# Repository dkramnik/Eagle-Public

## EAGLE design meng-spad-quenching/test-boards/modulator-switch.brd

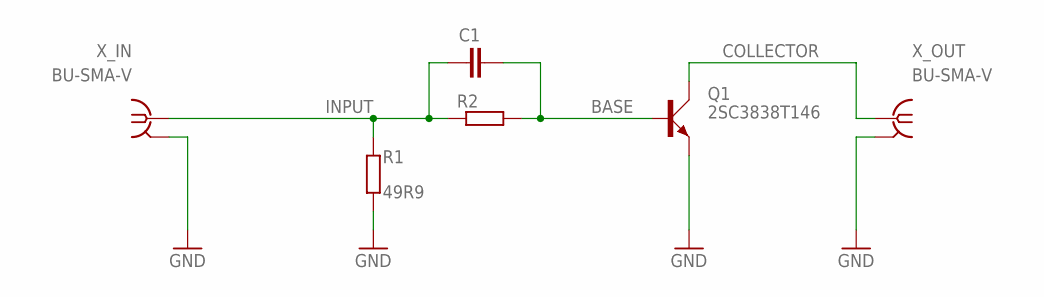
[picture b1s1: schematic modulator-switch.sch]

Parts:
C1: C-EUC0603; C0603
Q1: 2SC3838T146; SC59
R1: 49R9; R0805
R2: R-EU_R0603; R0603
X_IN: BU-SMA-V
X_OUT: BU-SMA-V

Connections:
BASE: C1.2, Q1.B, R2.2
COLLECTOR: Q1.C, X_OUT.1
GND: Q1.E, R1.2, X_IN.2 (GND), X_IN.3 (GND), X_IN.4 (GND), X_IN.5 (GND), X_OUT.2 (GND), X_OUT.3 (GND), X_OUT.4 (GND), X_OUT.5 (GND)
INPUT: C1.1, R1.1, R2.1, X_IN.1

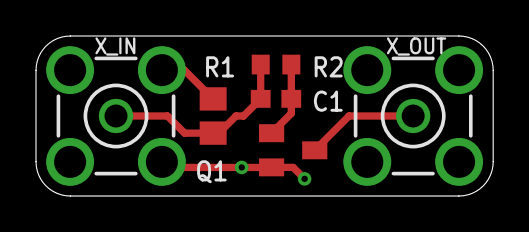
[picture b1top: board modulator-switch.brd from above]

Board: 2 copper layers, 25.4 x 8.9 mm, 6 parts (0 on the bottom side), 4 nets.

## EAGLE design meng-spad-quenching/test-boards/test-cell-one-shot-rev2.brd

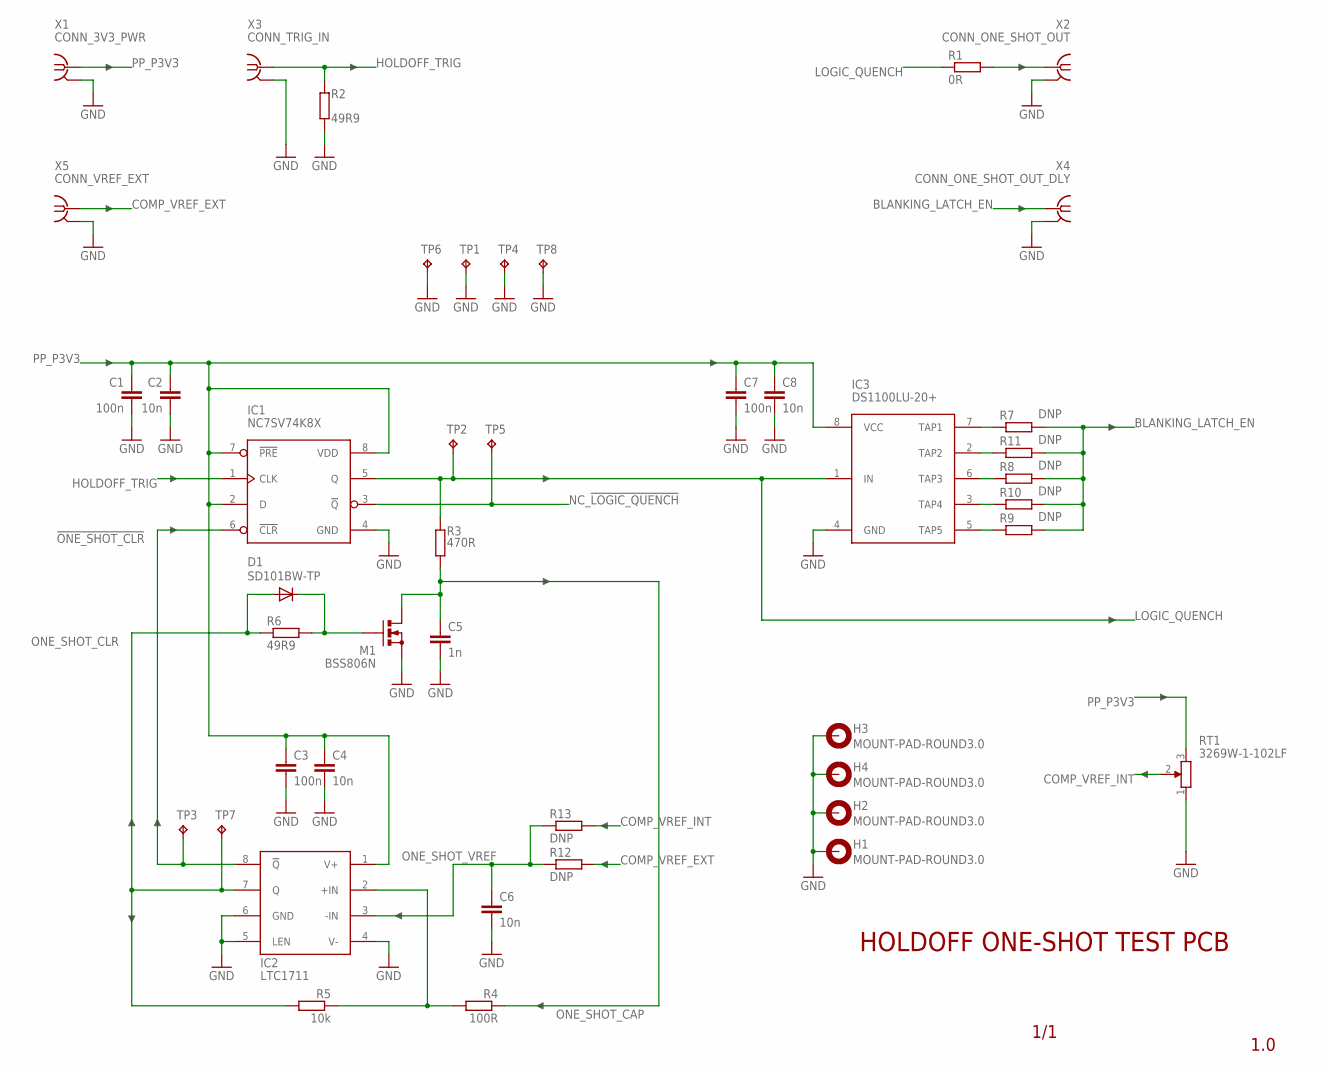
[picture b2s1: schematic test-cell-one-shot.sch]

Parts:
C1, C3, C7: 100n; C0402
C2, C4, C6, C8: 10n; C0402
C5: 1n; C0402
D1: SD101BW-TP; SOD123
H1, H2, H3, H4: MOUNT-PAD-ROUND3.0; 3,0-PAD
IC1: NC7SV74K8X; US8_3.1MM_JDEC_MO-187
IC2: LTC1711; US8_3.1MM_JDEC_MO-187
IC3: DS1100LU-20+; US8_3.1MM_JDEC_MO-187
M1: BSS806N; SOT23R_INFINEON
R1: 0R; R0402
R2: 49R9; R0603
R3: 470R; R0402
R4: 100R; R0402
R5: 10k; R0402
R6: 49R9; R0402
R7, R8, R9, R10, R11, R12, R13: DNP; R0402
RT1: 3269W-1-102LF; 3269W
TP1, TP2, TP3, TP4, TP5, TP6, TP7, TP8: TPTP10R; TP10R
X1: CONN_3V3_PWR; J502-ND-142-0711-871/876
X2: CONN_ONE_SHOT_OUT; J502-ND-142-0711-871/876
X3: CONN_TRIG_IN; J502-ND-142-0711-871/876
X4: CONN_ONE_SHOT_OUT_DLY; J502-ND-142-0711-871/876
X5: CONN_VREF_EXT; J502-ND-142-0711-871/876

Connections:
!ONE_SHOT_CLR: IC1.6 (!CLR), IC2.8 (!Q), TP3.TP
BLANKING_LATCH_EN: R7.1, R8.1, R9.1, R10.1, R11.1, X4.1
COMP_VREF_EXT: R12.1, X5.1
COMP_VREF_INT: R13.1, RT1.2
GND: C1.2, C2.2, C3.2, C4.2, C5.2, C6.2, C7.2, C8.2, H1.B3,0, H2.B3,0, H3.B3,0, H4.B3,0, IC1.4 (GND), IC2.4 (V-), IC2.5 (LEN), IC2.6 (GND), IC3.4 (GND), M1.2 (S), R2.2, RT1.1, TP1.TP, TP4.TP, TP6.TP, TP8.TP, X1.G@1 (GND), X1.G@2 (GND), X1.G@3 (GND), X1.G@4 (GND), X2.G@1 (GND), X2.G@2 (GND), X2.G@3 (GND), X2.G@4 (GND), X3.G@1 (GND), X3.G@2 (GND), X3.G@3 (GND), X3.G@4 (GND), X4.G@1 (GND), X4.G@2 (GND), X4.G@3 (GND), X4.G@4 (GND), X5.G@1 (GND), X5.G@2 (GND), X5.G@3 (GND), X5.G@4 (GND)
HOLDOFF_TRIG: IC1.1 (CLK), R2.1, X3.1
LOGIC_QUENCH: IC1.5 (Q), IC3.1 (IN), R1.2, R3.2, TP2.TP
unnamed: IC3.5 (TAP5), R9.2
unnamed: D1.C, M1.1 (G), R6.1
unnamed: R1.1, X2.1
unnamed: IC3.3 (TAP4), R10.2
unnamed: IC3.6 (TAP3), R8.2
unnamed: IC2.2 (+IN), R4.1, R5.2
unnamed: IC3.2 (TAP2), R11.2
unnamed: IC3.7 (TAP1), R7.2
NC_!LOGIC_QUENCH: IC1.3 (!Q), TP5.TP
ONE_SHOT_CAP: C5.1, M1.3 (D), R3.1, R4.2
ONE_SHOT_CLR: D1.A, IC2.7 (Q), R5.1, R6.2, TP7.TP
ONE_SHOT_VREF: C6.1, IC2.3 (-IN), R12.2, R13.2
PP_P3V3: C1.1, C2.1, C3.1, C4.1, C7.1, C8.1, IC1.2 (D), IC1.7 (!PRE), IC1.8 (VDD), IC2.1 (V+), IC3.8 (VCC), RT1.3, X1.1

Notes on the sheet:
HOLDOFF ONE-SHOT TEST PCB
1/1
1.0

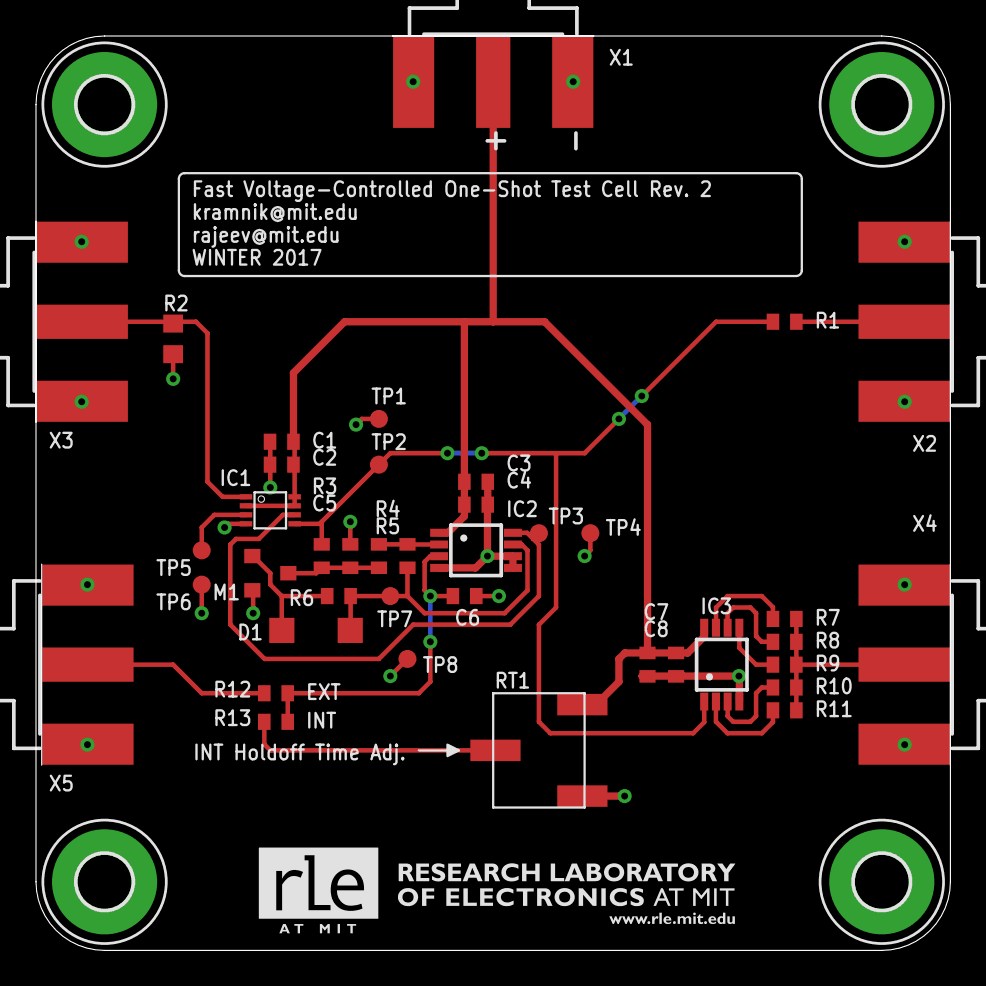
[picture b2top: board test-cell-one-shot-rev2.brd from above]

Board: 2 copper layers, 50.8 x 50.8 mm, 44 parts (0 on the bottom side), 20 nets.

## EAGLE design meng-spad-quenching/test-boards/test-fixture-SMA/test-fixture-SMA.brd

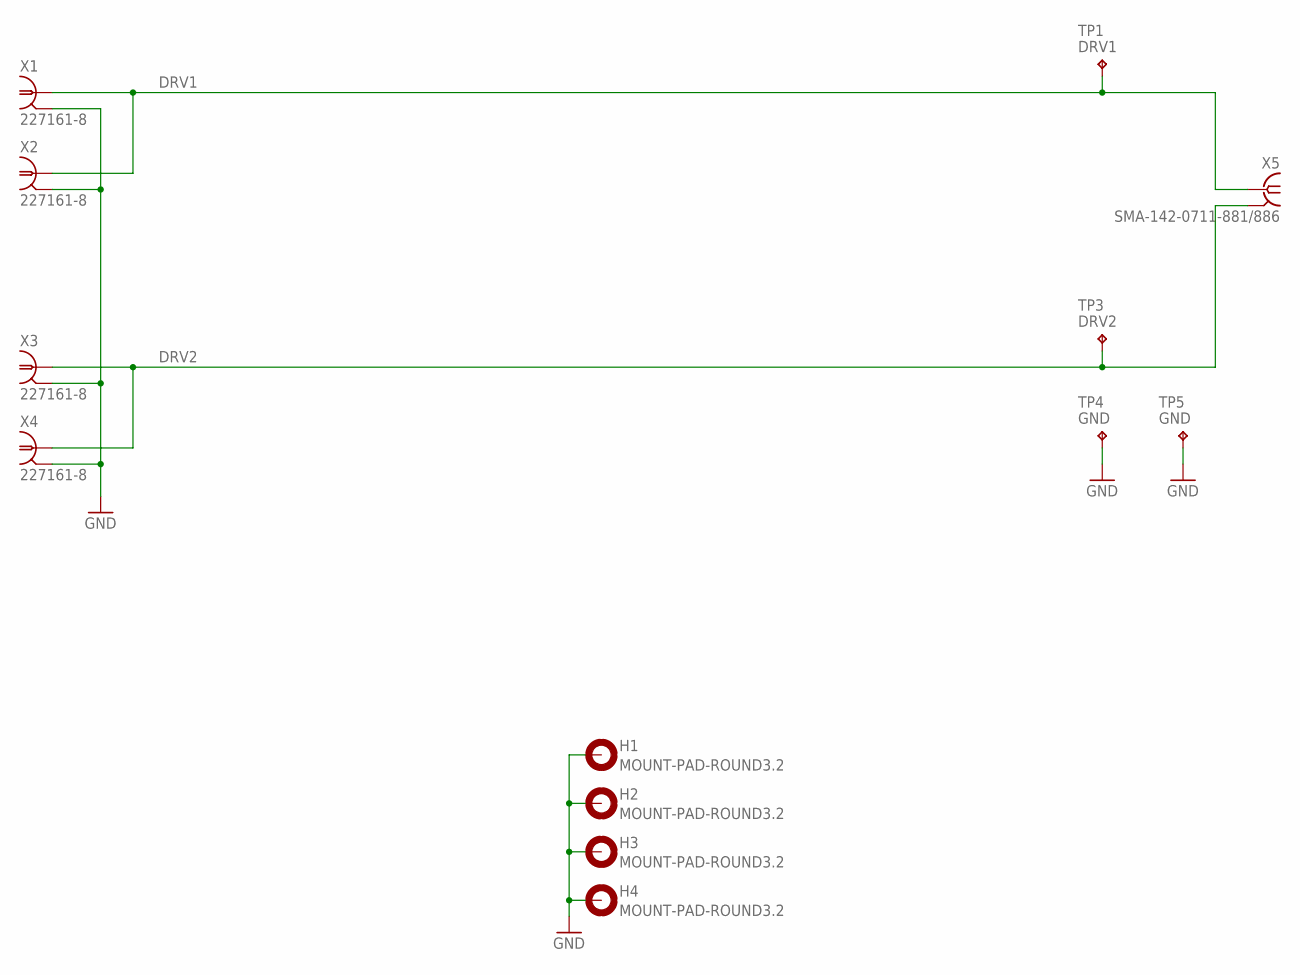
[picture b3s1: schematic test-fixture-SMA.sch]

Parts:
H1, H2, H3, H4: MOUNT-PAD-ROUND3.2; 3,2-PAD
TP1: DRV1; KEYSTONE_5000_MINIATURE
TP3: DRV2; KEYSTONE_5000_MINIATURE
TP4, TP5: GND; KEYSTONE_5000_MINIATURE
X1, X2, X3, X4: 227161-8; AMP_227161
X5: SMA-142-0711-881/886; J502-ND-142-0711-881/886

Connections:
DRV1: TP1.P$1, X1.1, X2.1, X5.1
DRV2: TP3.P$1, X3.1, X4.1, X5.G@1 (2), X5.G@2 (2), X5.G@3 (2), X5.G@4 (2)
GND: H1.B3,2, H2.B3,2, H3.B3,2, H4.B3,2, TP4.P$1, TP5.P$1, X1.2, X2.2, X3.2, X4.2

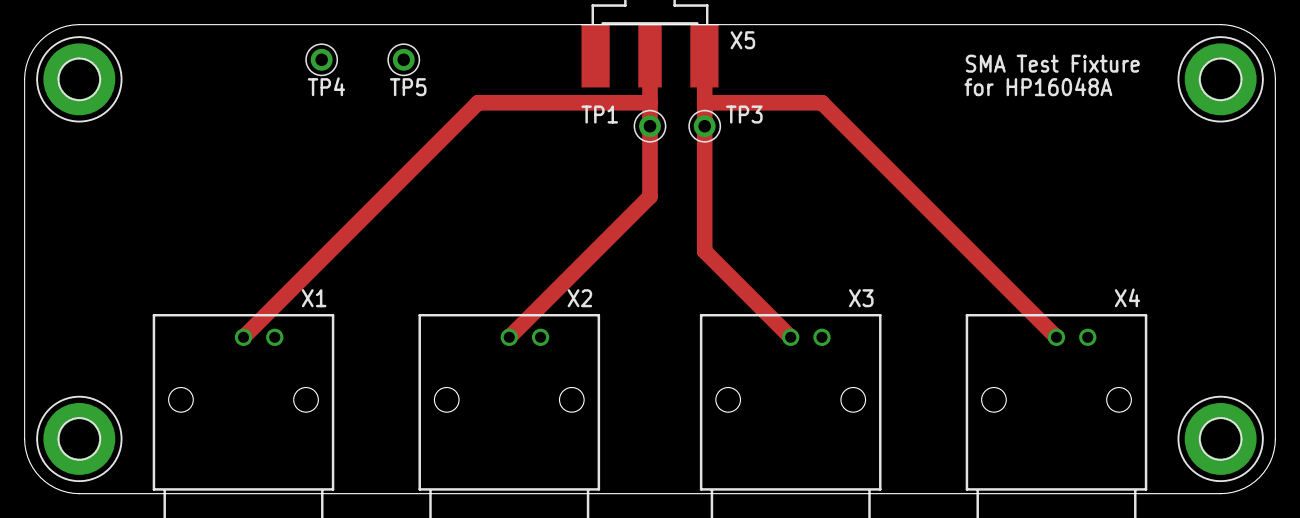
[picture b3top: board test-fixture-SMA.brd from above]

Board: 2 copper layers, 101.6 x 38.1 mm, 13 parts (0 on the bottom side), 3 nets.

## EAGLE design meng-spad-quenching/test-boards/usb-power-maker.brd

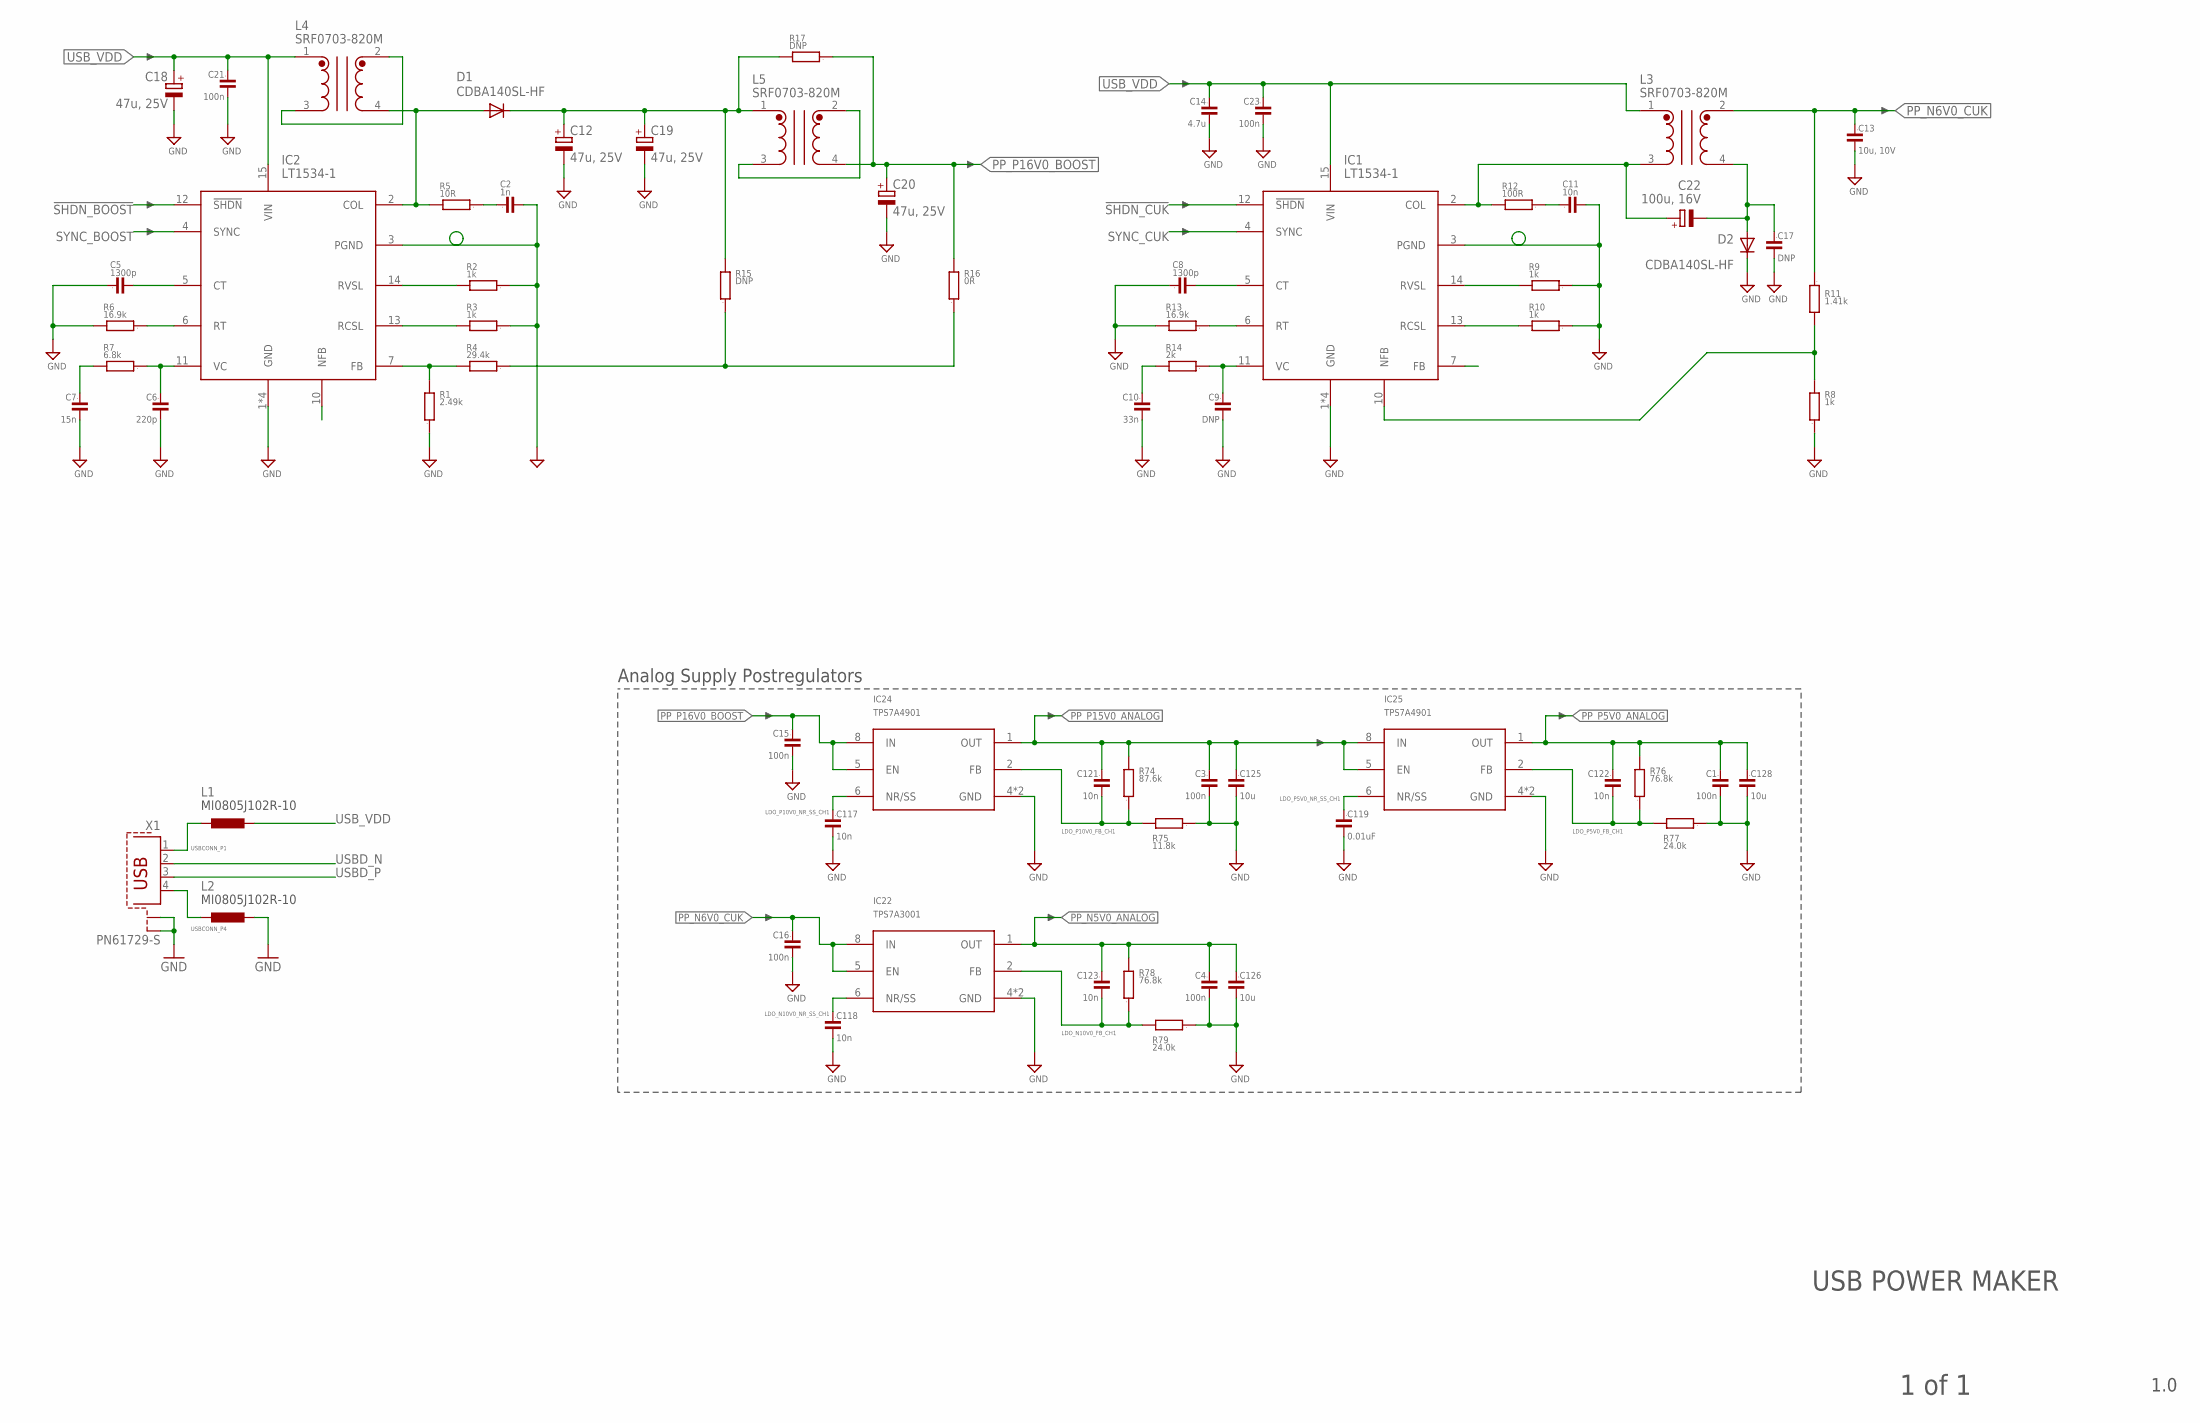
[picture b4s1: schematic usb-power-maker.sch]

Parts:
C1, C3, C4, C15, C16, C21, C23: 100n; 0603
C2: 1n; 0603
C5, C8: 1300p; 0603
C6: 220p; 0603
C7: 15n; 0603
C9, C17: DNP; 0603
C10: 33n; 0603
C11, C117, C118, C121, C122, C123: 10n; 0603
C12, C18, C19, C20: 47u, 25V; E2,5-6
C13: 10u, 10V; 0805
C14: 4.7u; 0805
C22: 100u, 16V; E2,5-6
C119: 0.01uF; 0603
C125, C126, C128: 10u; 0805
D1, D2: CDBA140SL-HF; DO214AC
IC1, IC2: LT1534-1; SO16
IC22: TPS7A3001; MSOP-8_POWER_PAD
IC24, IC25: TPS7A4901; MSOP-8_POWER_PAD
L1, L2: MI0805J102R-10; R0805
L3, L4, L5: SRF0703-820M; SRF0703
R1: 2.49k; 0603
R2, R3, R8, R9, R10: 1k; 0603
R4: 29.4k; 0603
R5: 10R; 0603
R6, R13: 16.9k; 0603
R7: 6.8k; 0603
R11: 1.41k; 0603
R12: 100R; 0603
R14: 2k; 0603
R15, R17: DNP; 0603
R16: 0R; 0603
R74: 87.6k; 0603
R75: 11.8k; 0603
R76, R78: 76.8k; 0603
R77, R79: 24.0k; 0603
X1: PN61729-S

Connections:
!SHDN_BOOST: IC2.12 (!SHDN)
!SHDN_CUK: IC1.12 (!SHDN)
BOOST_STAGE1: C12.+, C19.+, D1.C, L5.1, R15.2, R17.2
GND: C1.2, C2.2, C3.2, C4.2, C5.1, C6.2, C7.2, C8.1, C9.2, C10.2, C11.2, C12.-, C13.2, C14.2, C15.2, C16.2, C17.2, C18.-, C19.-, C20.-, C21.2, C23.2, C117.2, C118.2, C119.2, C125.2, C126.2, C128.2, D2.C, IC1.1 (GND), IC1.3 (PGND), IC1.8 (GND), IC1.9 (GND), IC1.16 (GND), IC2.1 (GND), IC2.3 (PGND), IC2.8 (GND), IC2.9 (GND), IC2.16 (GND), IC22.4 (GND), IC22.PAD (GND), IC24.4 (GND), IC24.PAD (GND), IC25.4 (GND), IC25.PAD (GND), L2.2, R1.1, R2.1, R3.1, R6.2, R8.1, R9.1, R10.1, R13.2, R75.1, R77.1, R79.1, X1.S1, X1.S2
LDO_N10V0_FB_CH1: C123.2, IC22.2 (FB), R78.1, R79.2
LDO_N10V0_NR_SS_CH1: C118.1, IC22.6 (NR/SS)
LDO_P5V0_FB_CH1: C122.2, IC25.2 (FB), R76.1, R77.2
LDO_P5V0_NR_SS_CH1: C119.1, IC25.6 (NR/SS)
LDO_P10V0_FB_CH1: C121.2, IC24.2 (FB), R74.1, R75.2
LDO_P10V0_NR_SS_CH1: C117.1, IC24.6 (NR/SS)
unnamed: IC2.7 (FB), R1.2, R4.2
unnamed: IC2.13 (RCSL), R3.2
unnamed: L4.2, L4.3
unnamed: L5.2, L5.3
unnamed: IC2.14 (RVSL), R2.2
unnamed: D1.A, IC2.2 (COL), L4.4, R5.2
unnamed: C2.1, R5.1
unnamed: C7.1, R7.2
unnamed: R4.1, R15.1, R16.1
unnamed: IC1.13 (RCSL), R10.2
unnamed: C6.1, IC2.11 (VC), R7.1
unnamed: IC2.6 (RT), R6.1
unnamed: C5.2, IC2.5 (CT)
unnamed: IC1.14 (RVSL), R9.2
unnamed: C17.1, C22.-, D2.A, L3.4
unnamed: C11.1, R12.1
unnamed: C10.1, R14.2
unnamed: C9.1, IC1.11 (VC), R14.1
unnamed: IC1.6 (RT), R13.1
unnamed: C8.2, IC1.5 (CT)
unnamed: IC1.10 (NFB), R8.2, R11.2
unnamed: C22.+, IC1.2 (COL), L3.3, R12.2
PP_N5V0_ANALOG: C4.1, C123.1, C126.1, IC22.1 (OUT), R78.2
PP_N6V0_CUK: C13.1, C16.1, IC22.5 (EN), IC22.8 (IN), L3.2, R11.1
PP_P5V0_ANALOG: C1.1, C122.1, C128.1, IC25.1 (OUT), R76.2
PP_P15V0_ANALOG: C3.1, C121.1, C125.1, IC24.1 (OUT), IC25.5 (EN), IC25.8 (IN), R74.2
PP_P16V0_BOOST: C15.1, C20.+, IC24.5 (EN), IC24.8 (IN), L5.4, R16.2, R17.1
SYNC_BOOST: IC2.4 (SYNC)
SYNC_CUK: IC1.4 (SYNC)
USBCONN_P1: L1.1, X1.1
USBCONN_P4: L2.1, X1.4
USBD_N: X1.2
USBD_P: X1.3
USB_VDD: C14.1, C18.+, C21.1, C23.1, IC1.15 (VIN), IC2.15 (VIN), L1.2, L3.1, L4.1

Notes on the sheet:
USB POWER MAKER
1.0
1 of 1
Analog Supply Postregulators

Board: 2 copper layers, 68 parts (0 on the bottom side), 38 nets, no tracks yet.

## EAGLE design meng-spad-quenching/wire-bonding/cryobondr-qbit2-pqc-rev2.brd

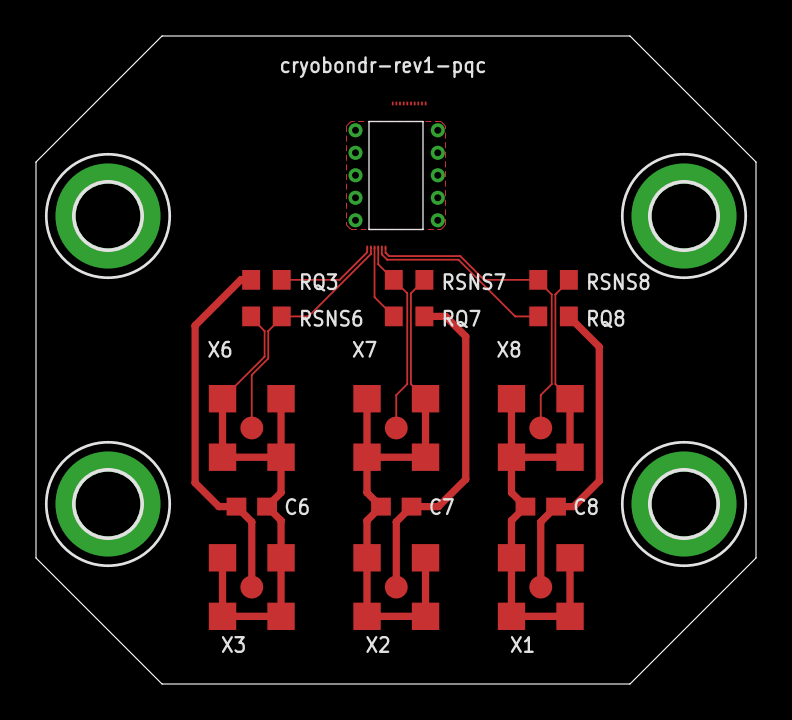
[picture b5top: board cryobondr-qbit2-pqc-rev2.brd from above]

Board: 2 copper layers, 40.0 x 36.0 mm, 20 parts (0 on the bottom side), 13 nets.

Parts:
C6, C7, C8: C0603
H1, H2, H3, H4: MOUNT-PAD-ROUND3.6; 3,6-PAD
IC1: QBIT2-WIREBOND-CRYO1
RQ3, RQ7, RQ8: 68k; R0603
RSNS6, RSNS7, RSNS8: DNP; R0603
X1: D8_BIAS; MMCX-SMT-BIGPADS
X2: D7_BIAS; MMCX-SMT-BIGPADS
X3: D6_BIAS; MMCX-SMT-BIGPADS
X6: D6_SENSE; MMCX-SMT-BIGPADS
X7: D7_SENSE; MMCX-SMT-BIGPADS
X8: D8_SENSE; MMCX-SMT-BIGPADS

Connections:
D6-N-CATHODE: IC1.D6-N-CATHODE, RQ3.2
D6-P-ANODE: IC1.D6-P-ANODE, RSNS6.1, X6.S
D6_BIAS: C6.1, RQ3.1, X3.S
D6_BIAS_RET: C6.2, RSNS6.2, X3.G1, X3.G2, X3.G3, X3.G4, X6.G1, X6.G2, X6.G3, X6.G4
D7-N-CATHODE: IC1.D7-N-CATHODE, RQ7.2
D7-P-ANODE: IC1.D7-P-ANODE, RSNS7.1, X7.S
D7_BIAS: C7.1, RQ7.1, X2.S
D7_BIAS_RET: C7.2, RSNS7.2, X2.G1, X2.G2, X2.G3, X2.G4, X7.G1, X7.G2, X7.G3, X7.G4
D8-N-CATHODE: IC1.D8-N-CATHODE, RQ8.2
D8-P-ANODE: IC1.D8-P-ANODE, RSNS8.1, X8.S
D8_BIAS: C8.1, RQ8.1, X1.S
D8_BIAS_RET: C8.2, RSNS8.2, X1.G1, X1.G2, X1.G3, X1.G4, X8.G1, X8.G2, X8.G3, X8.G4
GND: H1.B3,6, H2.B3,6, H3.B3,6, H4.B3,6

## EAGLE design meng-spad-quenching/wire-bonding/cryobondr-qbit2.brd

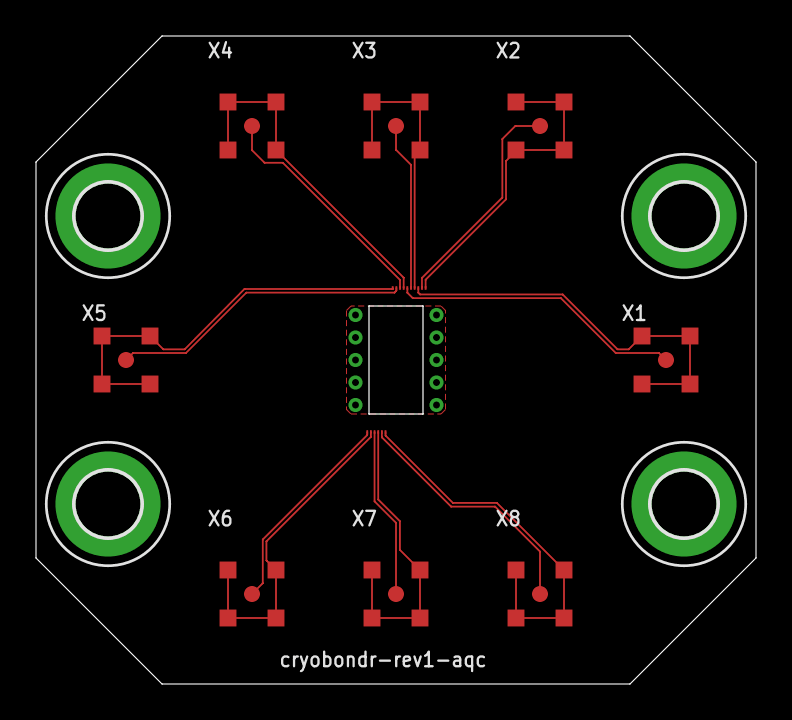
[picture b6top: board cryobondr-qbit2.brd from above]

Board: 2 copper layers, 40.0 x 36.0 mm, 13 parts (0 on the bottom side), 17 nets.

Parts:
H1, H2, H3, H4: MOUNT-PAD-ROUND3.6; 3,6-PAD
IC1: QBIT2-WIREBOND-CRYO1
X1: CONN-D3; MMCX-SMT
X2: CONN-D5; MMCX-SMT
X3: CONN-D4; MMCX-SMT
X4: CONN-D2; MMCX-SMT
X5: CONN-D1; MMCX-SMT
X6: CONN-D6; MMCX-SMT
X7: CONN-D7; MMCX-SMT
X8: CONN-D8; MMCX-SMT

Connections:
D1-N-CATHODE: IC1.D1-N-CATHODE, X5.S
D1-P-ANODE: IC1.D1-P-ANODE, X5.G1, X5.G2, X5.G3, X5.G4
D2-N-CATHODE: IC1.D2-N-CATHODE, X4.S
D2-P-ANODE: IC1.D2-P-ANODE, X4.G1, X4.G2, X4.G3, X4.G4
D3-N-CATHODE: IC1.D3-N-CATHODE, X1.S
D3-P-ANODE: IC1.D3-P-ANODE, X1.G1, X1.G2, X1.G3, X1.G4
D4-N-CATHODE: IC1.D4-N-CATHODE, X3.S
D4-P-ANODE: IC1.D4-P-ANODE, X3.G1, X3.G2, X3.G3, X3.G4
D5-N-CATHODE: IC1.D5-N-CATHODE, X2.S
D5-P-ANODE: IC1.D5-P-ANODE, X2.G1, X2.G2, X2.G3, X2.G4
D6-N-CATHODE: IC1.D6-N-CATHODE, X6.S
D6-P-ANODE: IC1.D6-P-ANODE, X6.G1, X6.G2, X6.G3, X6.G4
D7-N-CATHODE: IC1.D7-N-CATHODE, X7.S
D7-P-ANODE: IC1.D7-P-ANODE, X7.G1, X7.G2, X7.G3, X7.G4
D8-N-CATHODE: IC1.D8-N-CATHODE, X8.S
D8-P-ANODE: IC1.D8-P-ANODE, X8.G1, X8.G2, X8.G3, X8.G4
GND: H1.B3,6, H2.B3,6, H3.B3,6, H4.B3,6

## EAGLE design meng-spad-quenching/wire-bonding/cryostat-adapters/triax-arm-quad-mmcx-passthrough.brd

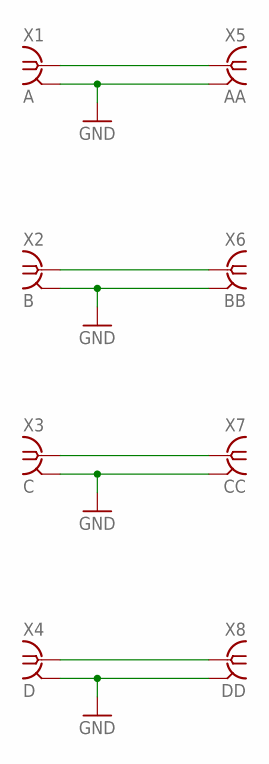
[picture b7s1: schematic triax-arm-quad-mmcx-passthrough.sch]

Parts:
X1: A; MMCX-J-P-X-ST-EM1-MKT
X2: B; MMCX-J-P-X-ST-EM1-MKT
X3: C; MMCX-J-P-X-ST-EM1-MKT
X4: D; MMCX-J-P-X-ST-EM1-MKT
X5: AA; MMCX-J-P-X-ST-EM1-MKT
X6: BB; MMCX-J-P-X-ST-EM1-MKT
X7: CC; MMCX-J-P-X-ST-EM1-MKT
X8: DD; MMCX-J-P-X-ST-EM1-MKT

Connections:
A: X1.1, X5.1
B: X2.1, X6.1
C: X3.1, X7.1
D: X4.1, X8.1
GND: X1.2@1 (GND), X1.2@2 (GND), X1.2@3 (GND), X1.2@4 (GND), X2.2@1 (GND), X2.2@2 (GND), X2.2@3 (GND), X2.2@4 (GND), X3.2@1 (GND), X3.2@2 (GND), X3.2@3 (GND), X3.2@4 (GND), X4.2@1 (GND), X4.2@2 (GND), X4.2@3 (GND), X4.2@4 (GND), X5.2@1 (GND), X5.2@2 (GND), X5.2@3 (GND), X5.2@4 (GND), X6.2@1 (GND), X6.2@2 (GND), X6.2@3 (GND), X6.2@4 (GND), X7.2@1 (GND), X7.2@2 (GND), X7.2@3 (GND), X7.2@4 (GND), X8.2@1 (GND), X8.2@2 (GND), X8.2@3 (GND), X8.2@4 (GND)

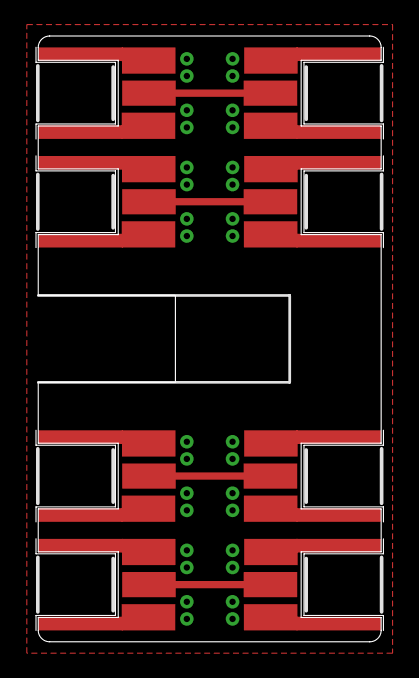
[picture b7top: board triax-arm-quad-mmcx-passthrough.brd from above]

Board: 2 copper layers, 19.1 x 33.7 mm, 8 parts (0 on the bottom side), 5 nets.
